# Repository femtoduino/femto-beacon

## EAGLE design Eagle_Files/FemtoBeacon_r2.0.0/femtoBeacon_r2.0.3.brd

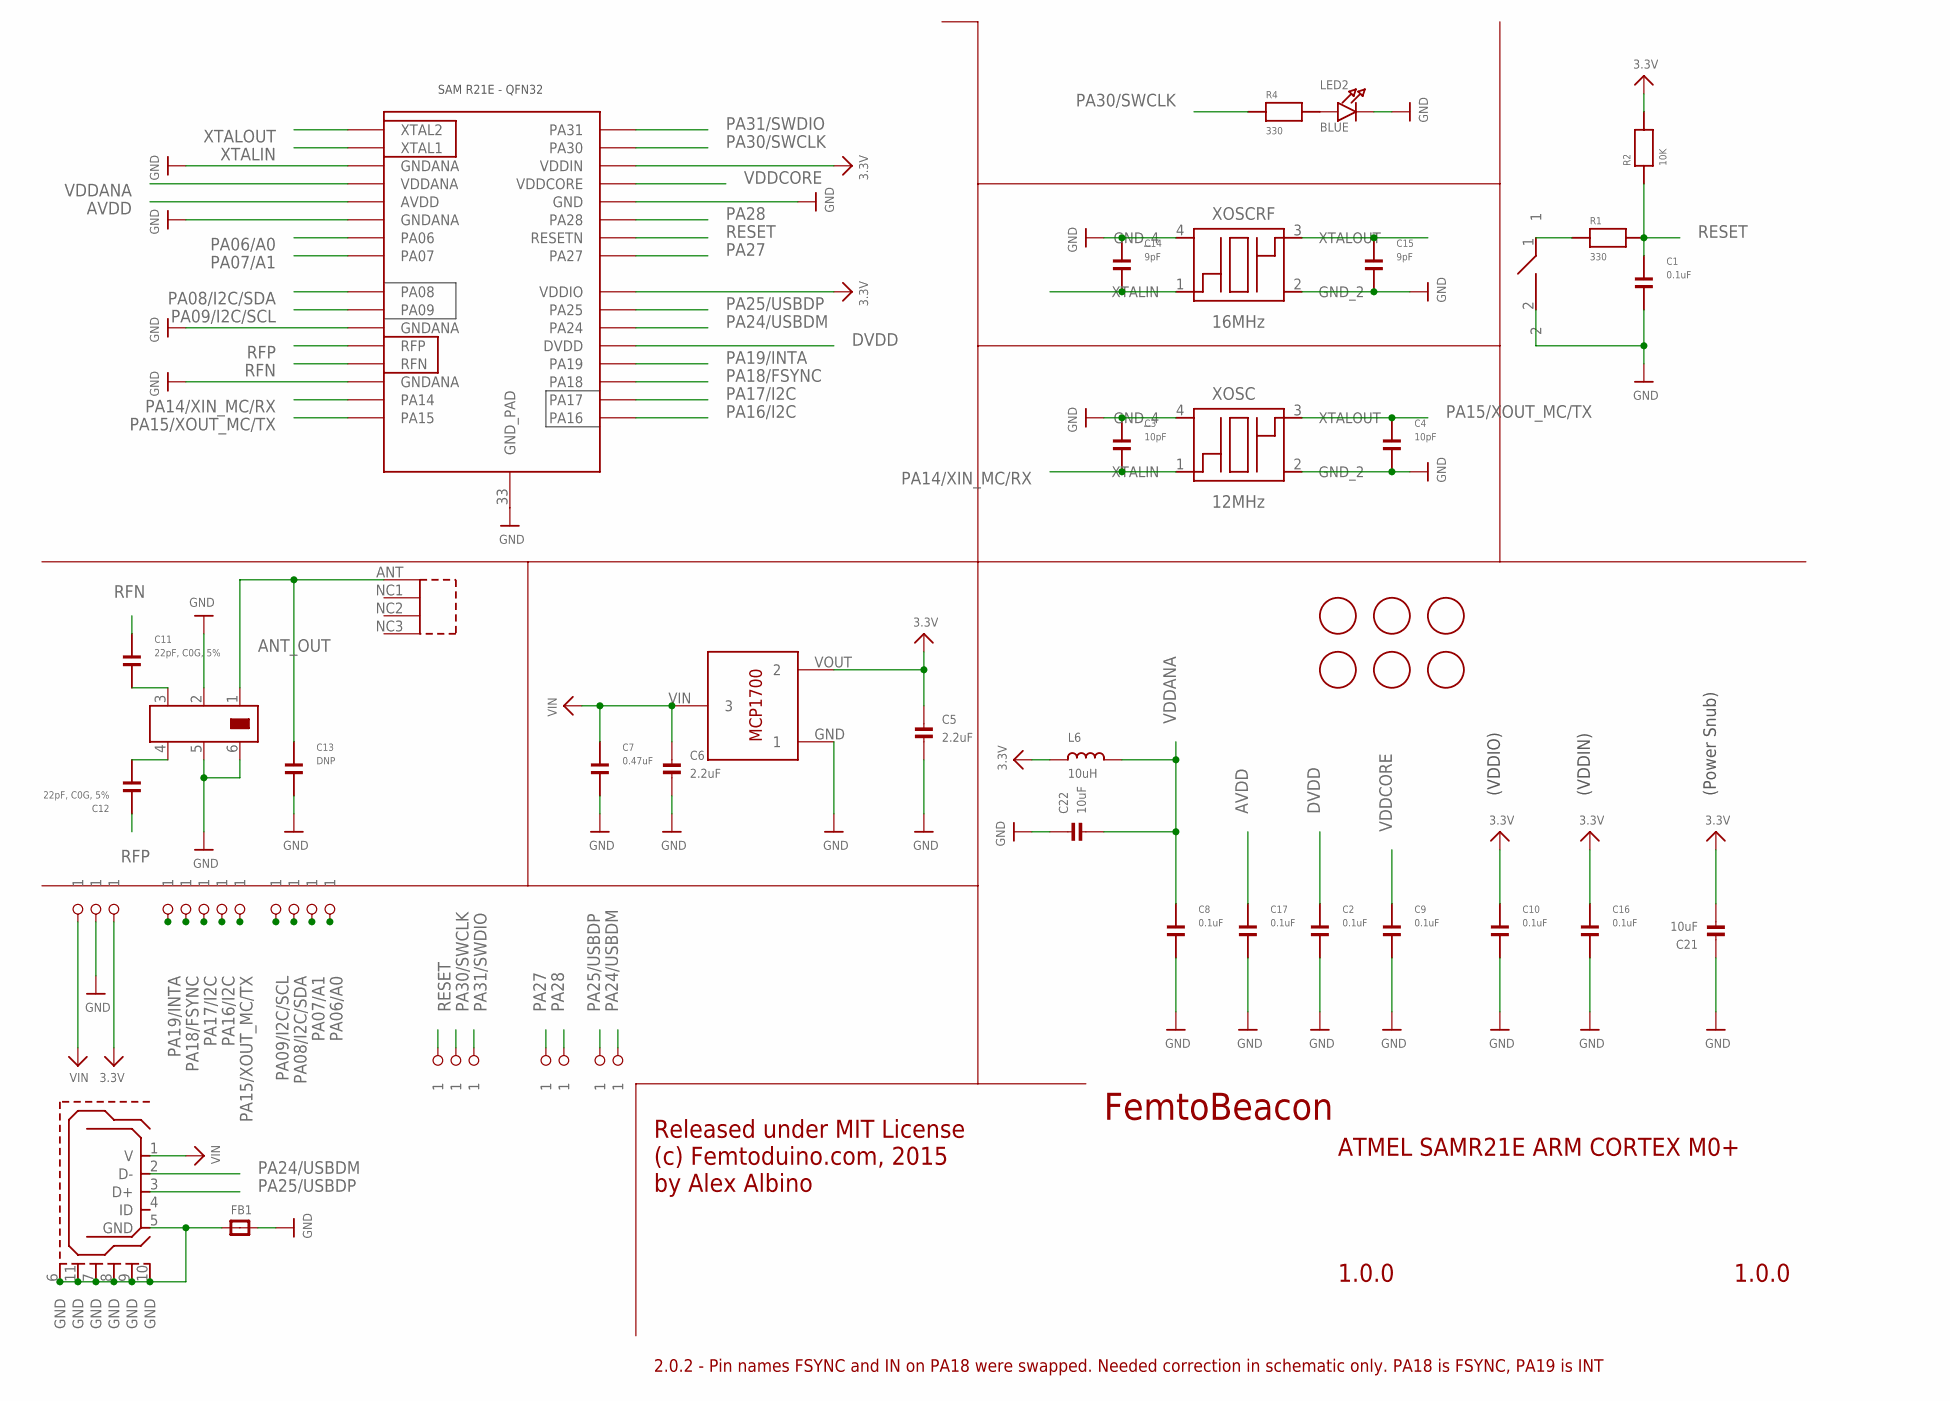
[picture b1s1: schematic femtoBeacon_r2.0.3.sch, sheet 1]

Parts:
BAL: JOHANSON_2450BM15A0015E; 0805_BALUN
BTN: DNP; SPST_SMD
C1, C8, C9, C10, C16, C17: 0.1uF; PART; DIGIKEY_PART 490-3194-1-ND
C2: 0.1uF; PART
C3, C4: 10pF; PART; DIGIKEY_PART 490-3194-1-ND
C5, C6: 2.2uF; _0402MP
C7: 0.47uF; PART
C11, C12: 22pF, C0G, 5%; PART; DIGIKEY_PART 490-3194-1-ND
C13: DNP; PART; DIGIKEY_PART 490-3194-1-ND
C14, C15: 9pF; PART; DIGIKEY_PART 490-3194-1-ND
C21, C22: 10uF; _0402MP
FB1: FERRITE_0603MP; _0603MP
FID1, FID2, FID3, FID4, FID5, FID6: FIDUCIAL; FIDUCIAL_1MM
IC: ATSAMR21E18A-MUT; QFN32
L6: 10uH; _0603MP
LDO_VREG: MCP1700T-3302E/TT
LED2: BLUE; CHIPLED_0603_NOOUTLINE
R1, R4: 330; PART
R2: 10K; PART
U$1, U$2, U$5, U$7, U$9, U$10, U$35, U$36, U$37, U$38, U$39, U$41, U$42, U$43, U$45, U$46, U$47, U$48, U$54: 1X1_ROUND
U$8: 0479480001
USB: USB_MICROB; USB_MICROB_PACKAGE
XOSC: 12MHz; TSX-3225
XOSCRF: 16MHz; TSX-3225

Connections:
3.3V: C5.1, C10.1, C16.1, C21.2, IC.24 (VDDIO), IC.30 (VDDIN), L6.1, LDO_VREG.VOUT (2), R2.2, U$5.P$1; also elsewhere on the board
ANT_OUT: BAL.1, C13.1, U$8.ANT (1)
AVDD: C17.1, IC.5 (AVDD)
DVDD: C2.1, IC.21 (DVDD)
GND: BAL.2, BAL.5, BAL.6, BTN.2, C1.2, C2.2, C3.1, C4.2, C5.2, C6.2, C7.2, C8.2, C9.2, C10.2, C13.2, C14.1, C15.2, C16.2, C17.2, C21.1, C22.1, FB1.2, IC.3 (GNDANA), IC.6 (GNDANA), IC.11 (GNDANA), IC.14 (GNDANA), IC.28 (GND), IC.33 (GND_PAD), LDO_VREG.GND (1), LED2.C, U$2.P$1, XOSC.2 (GND_2), XOSC.4 (GND_4), XOSCRF.2 (GND_2), XOSCRF.4 (GND_4); also elsewhere on the board
unnamed: BAL.3, C11.2
unnamed: BAL.4, C12.2
unnamed: FB1.1, USB.5 (GND), USB.6 (GND), USB.7 (GND), USB.8 (GND), USB.9 (GND), USB.10 (GND), USB.11 (GND)
unnamed: LED2.A, R4.2
unnamed: BTN.1, R1.1
PA06/A0: IC.7 (PA06), U$54.P$1
PA07/A1: IC.8 (PA07), U$43.P$1
PA08/I2C/SDA: IC.9 (PA08), U$42.P$1; also elsewhere on the board
PA09/I2C/SCL: IC.10 (PA09), U$41.P$1; also elsewhere on the board
PA14/XIN_MC/RX: C3.2, IC.15 (PA14), XOSC.1 (XTALIN)
PA15/XOUT_MC/TX: C4.1, IC.16 (PA15), U$39.P$1, XOSC.3 (XTALOUT)
PA16/I2C: IC.17 (PA16), U$38.P$1
PA17/I2C: IC.18 (PA17), U$37.P$1
PA18/FSYNC: IC.19 (PA18), U$36.P$1; also elsewhere on the board
PA19/INTA: IC.20 (PA19), U$35.P$1; also elsewhere on the board
PA24/USBDM: IC.22 (PA24), U$9.P$1, USB.2 (D-)
PA25/USBDP: IC.23 (PA25), U$10.P$1, USB.3 (D+)
PA27: IC.25 (PA27), U$7.P$1
PA28: IC.27 (PA28), U$48.P$1
PA30/SWCLK: IC.31 (PA30), R4.1, U$46.P$1
PA31/SWDIO: IC.32 (PA31), U$47.P$1
RESET: C1.1, IC.26 (RESETN), R1.2, R2.1, U$45.P$1
RFN: C11.1, IC.13 (RFN)
RFP: C12.1, IC.12 (RFP)
VDDANA: C8.1, C22.2, IC.4 (VDDANA), L6.2
VDDCORE: C9.1, IC.29 (VDDCORE)
VIN: C6.1, C7.1, LDO_VREG.VIN (3), U$1.P$1, USB.1 (V)
XTALIN: C14.2, IC.2 (XTAL1), XOSCRF.1 (XTALIN)
XTALOUT: C15.1, IC.1 (XTAL2), XOSCRF.3 (XTALOUT)

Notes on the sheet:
FemtoBeacon
1.0.0
ATMEL SAMR21E ARM CORTEX M0+
Released under MIT License (c) Femtoduino.com, 2015 by Alex Albino
(Power Snub)
(VDDIO)
(VDDIN)
2.0.2 - Pin names FSYNC and IN on PA18 were swapped. Needed correction in schematic only. PA18 is FSYNC, PA19 is INT

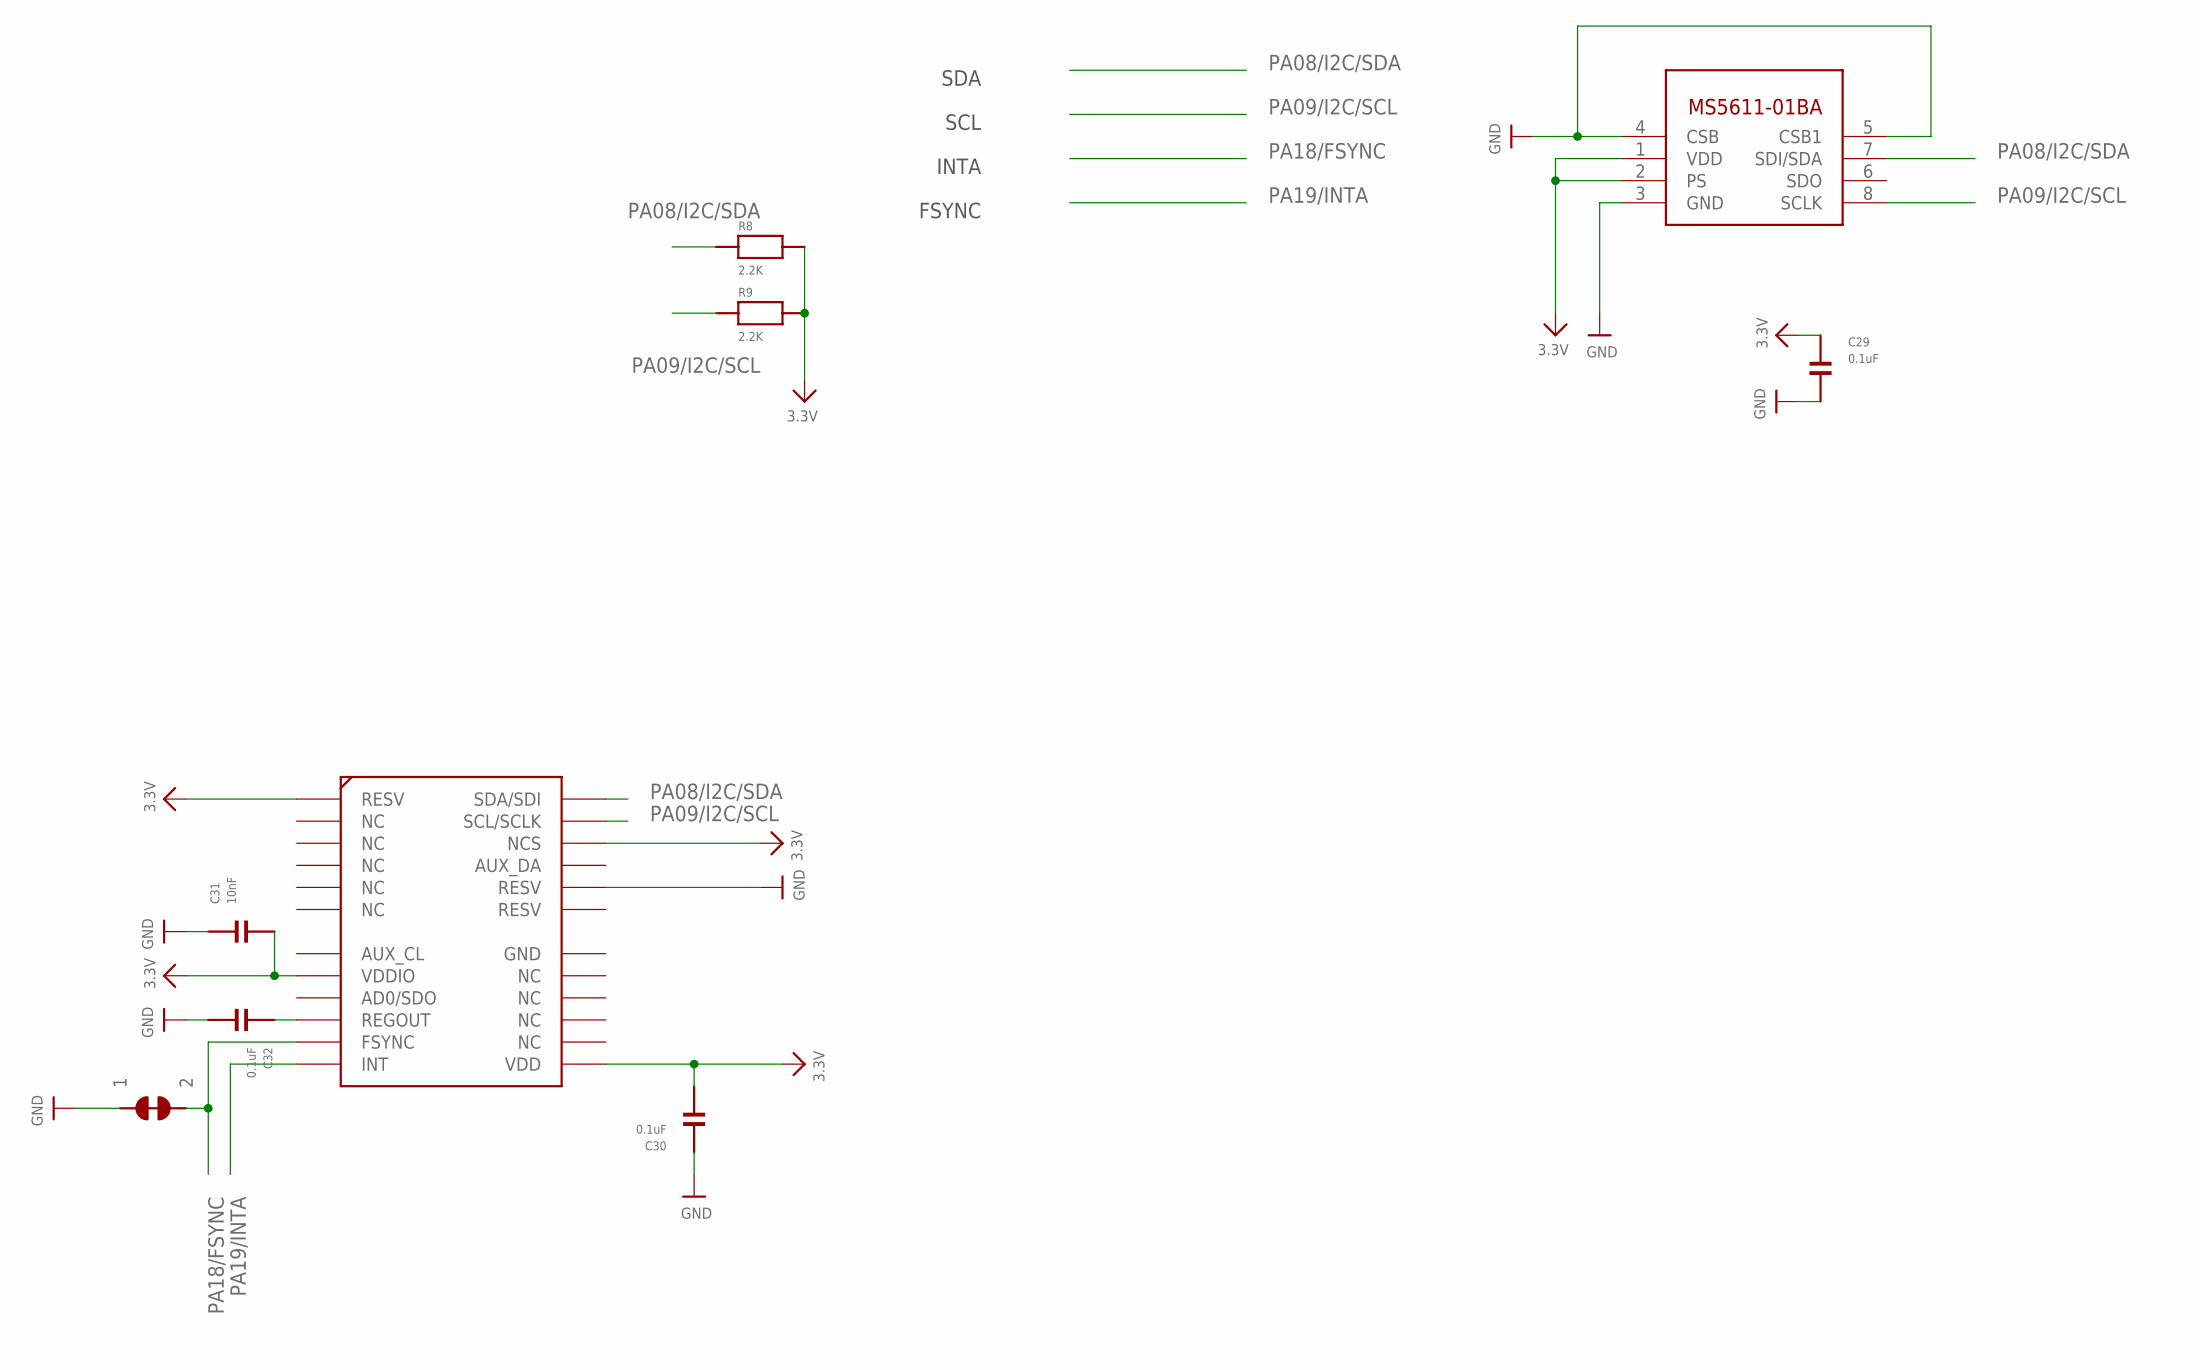
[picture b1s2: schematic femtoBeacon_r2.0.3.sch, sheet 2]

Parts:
BARO: MS5611-01BA03
C29, C30, C32: 0.1uF; PART; DIGIKEY_PART 490-3194-1-ND
C31: 10nF; PART; DIGIKEY_PART 490-3194-1-ND
IMU: MPU-9250; QFN_3X3MM
R8, R9: 2.2K; PART
SJ1: SOLDER_JUMPER_CLOSED; SOLDER_JUMP_CLOSED

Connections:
3.3V: BARO.1 (VDD), BARO.2 (PS), C29.1, C30.2, C31.2, IMU.P$1 (RESV), IMU.P$8 (VDDIO), IMU.P$13 (VDD), IMU.P$22 (NCS), R8.2, R9.2; also elsewhere on the board
GND: BARO.3 (GND), BARO.4 (CSB), BARO.5 (CSB1), C29.2, C30.1, C31.1, C32.2, IMU.P$20 (RESV), SJ1.1; also elsewhere on the board
unnamed: C32.1, IMU.P$10 (REGOUT)
PA08/I2C/SDA: BARO.7 (SDI/SDA), IMU.P$24 (SDA/SDI), R8.1; also elsewhere on the board
PA09/I2C/SCL: BARO.8 (SCLK), IMU.P$23 (SCL/SCLK), R9.1; also elsewhere on the board
PA18/FSYNC: IMU.P$11 (FSYNC), SJ1.2; also elsewhere on the board
PA19/INTA: IMU.P$12 (INT); also elsewhere on the board

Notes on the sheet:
SDA
SCL
INTA
FSYNC

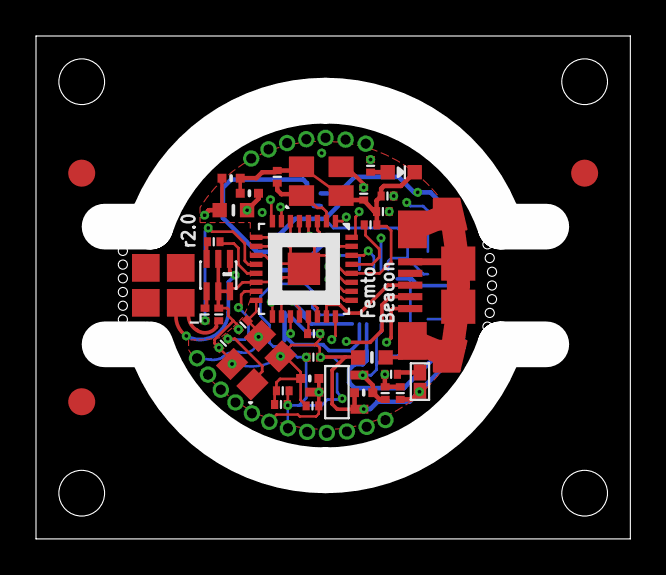
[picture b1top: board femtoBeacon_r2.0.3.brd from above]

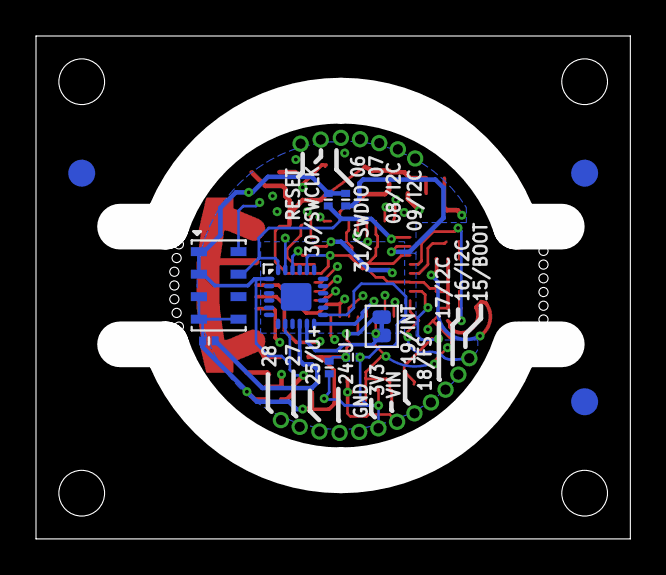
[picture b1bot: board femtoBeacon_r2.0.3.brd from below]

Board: 4 copper layers, 33.0 x 27.9 mm, 67 parts (11 on the bottom side), 35 nets.

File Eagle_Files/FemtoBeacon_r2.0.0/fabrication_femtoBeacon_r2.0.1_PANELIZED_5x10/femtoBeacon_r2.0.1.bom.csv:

"Qty","Value","Device","Package","Parts","Description","DIGIKEY_PART"
"1",,"FERRITE_0603MP","_0603MP","FB1","Ferrite Bead",
"10","0.1uF","CAPACITOR_0201","PART","C1, C2, C8, C9, C10, C16, C17, C29, C30, C32",,"490-3194-1-ND"
"1","0.47uF","CAPACITOR_0201","PART","C7",,
"1","10K","RESISTOR_0201","PART","R2",,
"1","10nF","CAPACITOR_0201","PART","C31",,"490-3194-1-ND"
"2","10pF","CAPACITOR_0201","PART","C3, C4",,"490-3194-1-ND"
"2","10uF","CAP_CERAMIC_0402MP","_0402MP","C21, C22","Ceramic Capacitors",
"1","10uH","INDUCTOR_0603MP","_0603MP","L6","Inductors",
"1","12MHz","TSX-3225","TSX-3225","XOSC",,
"1","16MHz","TSX-3225","TSX-3225","XOSCRF",,
"2","2.2K","RESISTOR_0201","PART","R8, R9",,
"2","2.2uF","CAP_CERAMIC_0402MP","_0402MP","C5, C6","Ceramic Capacitors",
"2","22pF, C0G, 5%","CAPACITOR_0201","PART","C11, C12",,"490-3194-1-ND"
"2","330","RESISTOR_0201","PART","R1, R4",,
"2","9pF","CAPACITOR_0201","PART","C14, C15",,"490-3194-1-ND"
"1","ATSAMR21E18A-MUT","ATSAMR21E18A-MUT","QFN32","IC","This is the ATMEL SAMR21E QFN-32. ATSAMR21E18A",
"1","BLUE","LED0603_NOOUTLINE","CHIPLED_0603_NOOUTLINE","LED2","LED",
"1","JOHANSON_2450BM15A0015E","JOHANSON_2450BM15A0015E","0805_BALUN","BAL",,
"1","MCP1700T-3302E/TT","MCP1700T-3302E/TT","MCP1700T-3302E/TT","LDO_VREG","Microchip LDO ""MCP1700"" in a 3-Pin SOT-23 package.",
"1","MPU-9250","MPU-9250","QFN_3X3MM","IMU",,
"1","MS5611-01BA03","MS5611-01BA03","MS5611-01BA03","BARO",,
"1","PULSE_ANT_2.4GHZ","PULSE_ANT_2.4GHZ","ANT_BAR","ANT1","Manufacturer part #W3008",
"1","USB_MICROB","USB_MICROB","USB_MICROB_PACKAGE","USB","This is the hirose ZX62-B-5PA(11) MICRO-USB B Type female connection.",

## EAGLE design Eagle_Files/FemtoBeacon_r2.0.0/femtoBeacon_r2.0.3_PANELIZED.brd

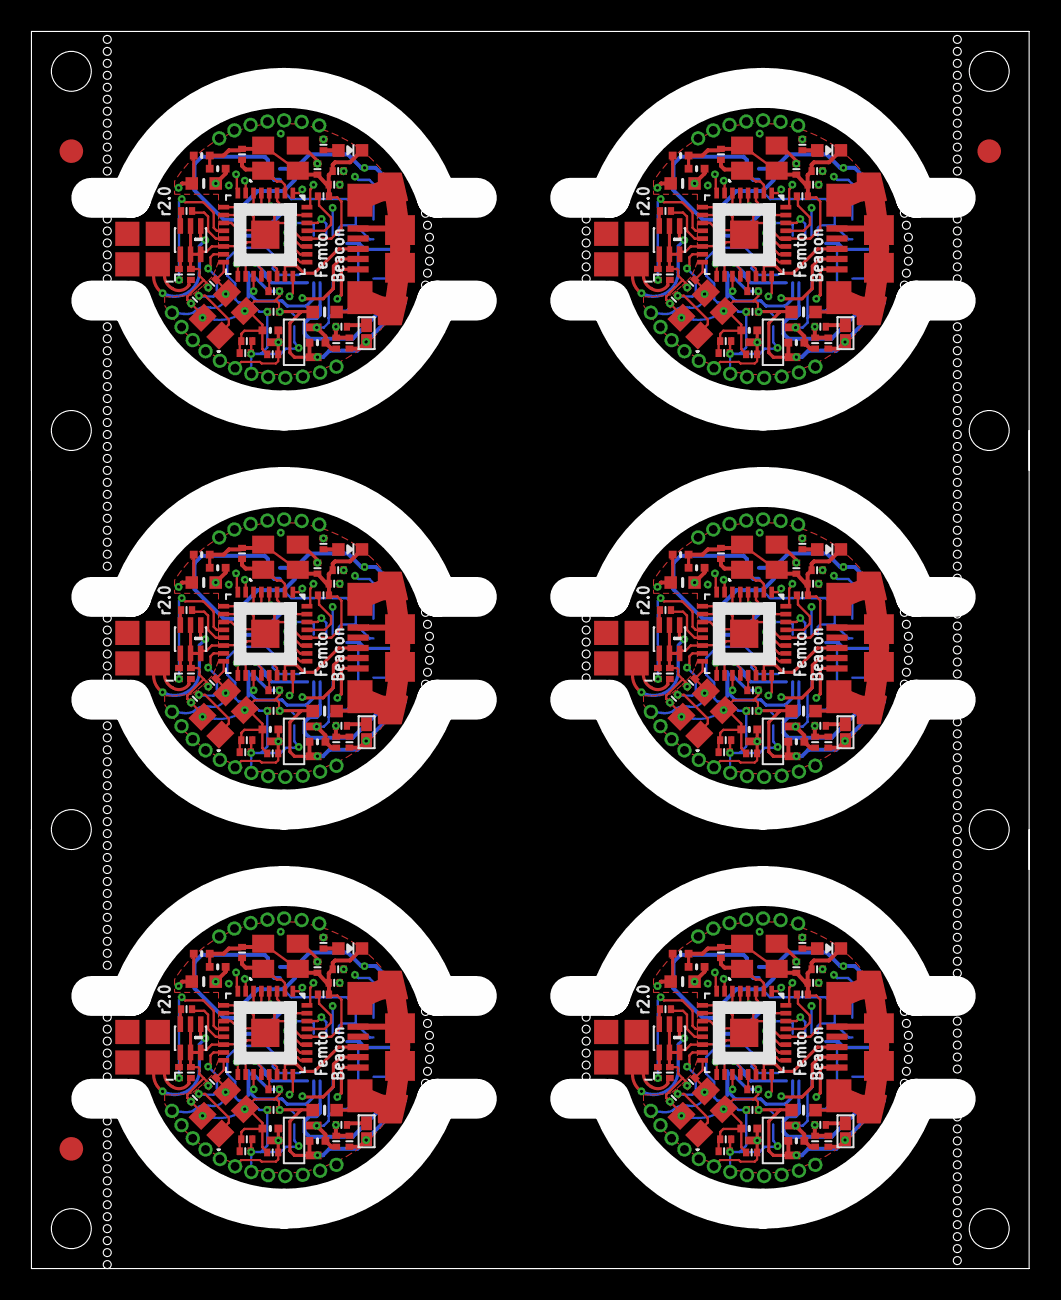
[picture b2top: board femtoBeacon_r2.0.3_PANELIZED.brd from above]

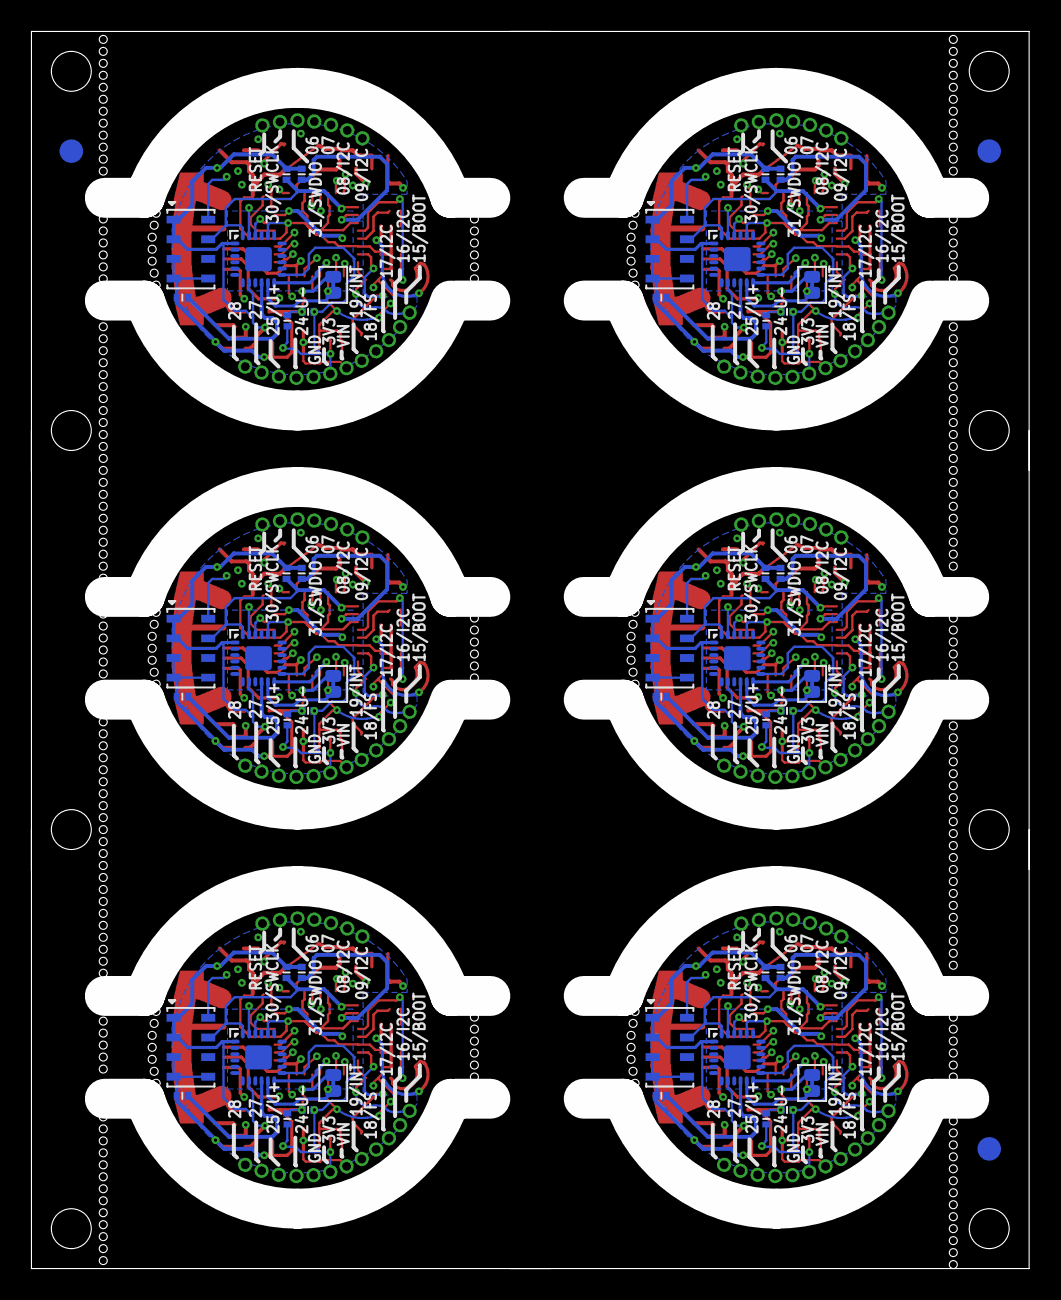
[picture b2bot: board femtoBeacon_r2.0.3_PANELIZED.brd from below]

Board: 4 copper layers, 63.5 x 78.7 mm, 372 parts (51 on the bottom side), 210 nets.

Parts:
BAL, BAL1, BAL2, BAL3, BAL4, BAL5: JOHANSON_2450BM15A0015E; 0805_BALUN
BARO, BARO1, BARO2, BARO3, BARO4, BARO5: MS5611-01BA03
BTN, BTN1, BTN2, BTN3, BTN4, BTN5: DNP; SPST_SMD
C1, C2, C8, C9, C10, C16, C17, C18, C19, C25, C26, C27, C28, C29, C30, C32, C33, C36, C45, C46, C47, C48, C52, C53, C54, C55, C56, C59, C68, C69, C70, C71, C75, C76, C77, C78, C79, C82, C91, C92, C93, C94, C98, C99, C100, C101, C102, C105, C114, C115, C116, C117, C121, C122, C123, C124, C125, C128, C137, C138: 0.1uF; PART
C3, C4, C37, C38, C60, C61, C83, C84, C106, C107, C129, C130: 10pF; PART
C5, C6, C20, C23, C49, C50, C72, C73, C95, C96, C118, C119: 2.2uF; _0402MP
C7, C24, C51, C74, C97, C120: 0.47uF; PART
C11, C12, C39, C40, C62, C63, C85, C86, C108, C109, C131, C132: 22pF, C0G, 5%; PART
C13, C41, C64, C87, C110, C133: DNP; PART
C14, C15, C42, C43, C65, C66, C88, C89, C111, C112, C134, C135: 9pF; PART
C21, C22, C34, C35, C57, C58, C80, C81, C103, C104, C126, C127: 10uF; _0402MP
C31, C44, C67, C90, C113, C136: 10nF; PART
FB1, FB2, FB3, FB4, FB5, FB6: _0603MP
FID1, FID2, FID3, FID4, FID5, FID6: FIDUCIAL; FIDUCIAL_1MM
IC, IC1, IC2, IC3, IC4, IC5: ATSAMR21E18A-MUT; QFN32
IMU, IMU1, IMU2, IMU3, IMU4, IMU5: MPU-9250; QFN_3X3MM
L1, L2, L3, L4, L5, L6: 10uH; _0603MP
LDO_VREG, LDO_VREG1, LDO_VREG2, LDO_VREG3, LDO_VREG4, LDO_VREG5: MCP1700T-3302E/TT
LED1, LED2, LED3, LED4, LED5, LED6: BLUE; CHIPLED_0603_NOOUTLINE
R1, R3, R4, R6, R11, R13, R16, R18, R21, R23, R26, R28: 330; PART
R2, R5, R12, R17, R22, R27: 10K; PART
R7, R8, R9, R10, R14, R15, R19, R20, R24, R25, R29, R30: 2.2K; PART
SJ1, SJ2, SJ3, SJ4, SJ5, SJ6: SOLDER_JUMPER_CLOSED; SOLDER_JUMP_CLOSED
U$1, U$2, U$3, U$4, U$5, U$6, U$7, U$9, U$10, U$11, U$12, U$13, U$14, U$15, U$16, U$17, U$18, U$19, U$20, U$21, U$22, U$23, U$24, U$25, U$26, U$28, U$29, U$30, U$31, U$32, U$33, U$34, U$35, U$36, U$37, U$38, U$39, U$40, U$41, U$42, U$43, U$44, U$45, U$46, U$47, U$48, U$49, U$50, U$51, U$52, U$53, U$54, U$55, U$56, U$57, U$58, U$59, U$61, U$62, U$63, U$64, U$65, U$66, U$67, U$68, U$69, U$70, U$71, U$72, U$73, U$74, U$75, U$76, U$77, U$78, U$79, U$81, U$82, U$83, U$84, U$85, U$86, U$87, U$88, U$89, U$90, U$91, U$92, U$93, U$94, U$95, U$96, U$97, U$98, U$99, U$101, U$102, U$103, U$104, U$105, U$106, U$107, U$108, U$109, U$110, U$111, U$112, U$113, U$114, U$115, U$116, U$117, U$118, U$119: 1X1_ROUND
U$8, U$27, U$60, U$80, U$100, U$120: 0479480001
USB, USB1, USB2, USB3, USB4, USB5: USB_MICROB; USB_MICROB_PACKAGE
XOSC, XOSC1, XOSC2, XOSC3, XOSC4, XOSC5: 12MHz; TSX-3225
XOSCRF, XOSCRF1, XOSCRF2, XOSCRF3, XOSCRF4, XOSCRF5: 16MHz; TSX-3225

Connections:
3.3V: BARO.1, BARO.2, C5.1, C10.1, C16.1, C21.2, C29.1, C30.2, C31.2, IC.24, IC.30, IMU.P$1, IMU.P$8, IMU.P$13, IMU.P$22, L6.1, LDO_VREG.VOUT, R2.2, R8.2, R9.2, U$5.P$1
3.3V1: BARO1.1, BARO1.2, C20.1, C25.1, C28.1, C34.2, C36.1, C44.2, C45.2, IC1.24, IC1.30, IMU1.P$1, IMU1.P$8, IMU1.P$13, IMU1.P$22, L1.1, LDO_VREG1.VOUT, R5.2, R7.2, R10.2, U$6.P$1
3.3V2: BARO2.1, BARO2.2, C49.1, C52.1, C55.1, C57.2, C59.1, C67.2, C68.2, IC2.24, IC2.30, IMU2.P$1, IMU2.P$8, IMU2.P$13, IMU2.P$22, L2.1, LDO_VREG2.VOUT, R12.2, R14.2, R15.2, U$30.P$1
3.3V3: BARO3.1, BARO3.2, C72.1, C75.1, C78.1, C80.2, C82.1, C90.2, C91.2, IC3.24, IC3.30, IMU3.P$1, IMU3.P$8, IMU3.P$13, IMU3.P$22, L3.1, LDO_VREG3.VOUT, R17.2, R19.2, R20.2, U$63.P$1
3.3V4: BARO4.1, BARO4.2, C95.1, C98.1, C101.1, C103.2, C105.1, C113.2, C114.2, IC4.24, IC4.30, IMU4.P$1, IMU4.P$8, IMU4.P$13, IMU4.P$22, L4.1, LDO_VREG4.VOUT, R22.2, R24.2, R25.2, U$83.P$1
3.3V5: BARO5.1, BARO5.2, C118.1, C121.1, C124.1, C126.2, C128.1, C136.2, C137.2, IC5.24, IC5.30, IMU5.P$1, IMU5.P$8, IMU5.P$13, IMU5.P$22, L5.1, LDO_VREG5.VOUT, R27.2, R29.2, R30.2, U$103.P$1
ANT_OUT: BAL.1, C13.1, U$8.ANT
ANT_OUT1: BAL1.1, C41.1, U$27.ANT
ANT_OUT2: BAL2.1, C64.1, U$60.ANT
ANT_OUT3: BAL3.1, C87.1, U$80.ANT
ANT_OUT4: BAL4.1, C110.1, U$100.ANT
ANT_OUT5: BAL5.1, C133.1, U$120.ANT
AVDD: C17.1, IC.5
AVDD1: C33.1, IC1.5
AVDD2: C56.1, IC2.5
AVDD3: C79.1, IC3.5
AVDD4: C102.1, IC4.5
AVDD5: C125.1, IC5.5
DVDD: C2.1, IC.21
DVDD1: C19.1, IC1.21
DVDD2: C48.1, IC2.21
DVDD3: C71.1, IC3.21
DVDD4: C94.1, IC4.21
DVDD5: C117.1, IC5.21
GND: BAL.2, BAL.5, BAL.6, BARO.3, BARO.4, BARO.5, BTN.2, C1.2, C2.2, C3.1, C4.2, C5.2, C6.2, C7.2, C8.2, C9.2, C10.2, C13.2, C14.1, C15.2, C16.2, C17.2, C21.1, C22.1, C29.2, C30.1, C31.1, C32.2, FB1.2, IC.3, IC.6, IC.11, IC.14, IC.28, IC.33, IMU.P$20, LDO_VREG.GND, LED2.C, SJ1.1, U$2.P$1, XOSC.2, XOSC.4, XOSCRF.2, XOSCRF.4
GND1: BAL1.2, BAL1.5, BAL1.6, BARO1.3, BARO1.4, BARO1.5, BTN1.2, C18.2, C19.2, C20.2, C23.2, C24.2, C25.2, C26.2, C27.2, C28.2, C33.2, C34.1, C35.1, C36.2, C37.1, C38.2, C41.2, C42.1, C43.2, C44.1, C45.1, C46.2, FB2.2, IC1.3, IC1.6, IC1.11, IC1.14, IC1.28, IC1.33, IMU1.P$20, LDO_VREG1.GND, LED1.C, SJ2.1, U$4.P$1, XOSC1.2, XOSC1.4, XOSCRF1.2, XOSCRF1.4
GND2: BAL2.2, BAL2.5, BAL2.6, BARO2.3, BARO2.4, BARO2.5, BTN2.2, C47.2, C48.2, C49.2, C50.2, C51.2, C52.2, C53.2, C54.2, C55.2, C56.2, C57.1, C58.1, C59.2, C60.1, C61.2, C64.2, C65.1, C66.2, C67.1, C68.1, C69.2, FB3.2, IC2.3, IC2.6, IC2.11, IC2.14, IC2.28, IC2.33, IMU2.P$20, LDO_VREG2.GND, LED3.C, SJ3.1, U$29.P$1, XOSC2.2, XOSC2.4, XOSCRF2.2, XOSCRF2.4
GND3: BAL3.2, BAL3.5, BAL3.6, BARO3.3, BARO3.4, BARO3.5, BTN3.2, C70.2, C71.2, C72.2, C73.2, C74.2, C75.2, C76.2, C77.2, C78.2, C79.2, C80.1, C81.1, C82.2, C83.1, C84.2, C87.2, C88.1, C89.2, C90.1, C91.1, C92.2, FB4.2, IC3.3, IC3.6, IC3.11, IC3.14, IC3.28, IC3.33, IMU3.P$20, LDO_VREG3.GND, LED4.C, SJ4.1, U$62.P$1, XOSC3.2, XOSC3.4, XOSCRF3.2, XOSCRF3.4
GND4: BAL4.2, BAL4.5, BAL4.6, BARO4.3, BARO4.4, BARO4.5, BTN4.2, C93.2, C94.2, C95.2, C96.2, C97.2, C98.2, C99.2, C100.2, C101.2, C102.2, C103.1, C104.1, C105.2, C106.1, C107.2, C110.2, C111.1, C112.2, C113.1, C114.1, C115.2, FB5.2, IC4.3, IC4.6, IC4.11, IC4.14, IC4.28, IC4.33, IMU4.P$20, LDO_VREG4.GND, LED5.C, SJ5.1, U$82.P$1, XOSC4.2, XOSC4.4, XOSCRF4.2, XOSCRF4.4
GND5: BAL5.2, BAL5.5, BAL5.6, BARO5.3, BARO5.4, BARO5.5, BTN5.2, C116.2, C117.2, C118.2, C119.2, C120.2, C121.2, C122.2, C123.2, C124.2, C125.2, C126.1, C127.1, C128.2, C129.1, C130.2, C133.2, C134.1, C135.2, C136.1, C137.1, C138.2, FB6.2, IC5.3, IC5.6, IC5.11, IC5.14, IC5.28, IC5.33, IMU5.P$20, LDO_VREG5.GND, LED6.C, SJ6.1, U$102.P$1, XOSC5.2, XOSC5.4, XOSCRF5.2, XOSCRF5.4
unnamed: BAL.3, C11.2
unnamed: BTN1.1, R3.1
unnamed: BAL.4, C12.2
unnamed: C32.1, IMU.P$10
unnamed: FB1.1, USB.5, USB.6, USB.7, USB.8, USB.9, USB.10, USB.11
unnamed: LED1.A, R6.2
unnamed: BAL1.3, C39.2
unnamed: BAL1.4, C40.2
unnamed: C46.1, IMU1.P$10
unnamed: FB2.1, USB1.5, USB1.6, USB1.7, USB1.8, USB1.9, USB1.10, USB1.11
unnamed: BTN2.1, R11.1
unnamed: LED3.A, R13.2
unnamed: LED2.A, R4.2
unnamed: BAL2.3, C62.2
unnamed: BAL2.4, C63.2
unnamed: C69.1, IMU2.P$10
unnamed: FB3.1, USB2.5, USB2.6, USB2.7, USB2.8, USB2.9, USB2.10, USB2.11
unnamed: BTN3.1, R16.1
unnamed: LED4.A, R18.2
unnamed: BAL3.3, C85.2
unnamed: BAL3.4, C86.2
unnamed: C92.1, IMU3.P$10
unnamed: FB4.1, USB3.5, USB3.6, USB3.7, USB3.8, USB3.9, USB3.10, USB3.11
unnamed: BTN4.1, R21.1
unnamed: LED5.A, R23.2
unnamed: BTN.1, R1.1
unnamed: BAL4.3, C108.2
unnamed: BAL4.4, C109.2
unnamed: C115.1, IMU4.P$10
unnamed: FB5.1, USB4.5, USB4.6, USB4.7, USB4.8, USB4.9, USB4.10, USB4.11
unnamed: BTN5.1, R26.1
unnamed: LED6.A, R28.2
unnamed: BAL5.3, C131.2
unnamed: BAL5.4, C132.2
unnamed: C138.1, IMU5.P$10
unnamed: FB6.1, USB5.5, USB5.6, USB5.7, USB5.8, USB5.9, USB5.10, USB5.11
PA1: IC1.25, U$22.P$1
PA2: IC1.27, U$23.P$1
PA3: IC2.25, U$55.P$1
PA4: IC2.27, U$56.P$1
PA5: IC3.25, U$75.P$1
PA6: IC3.27, U$76.P$1
PA06/A0: IC.7, U$54.P$1
PA06/A1: IC1.7, U$24.P$1
PA06/A2: IC2.7, U$57.P$1
PA06/A3: IC3.7, U$77.P$1
PA06/A4: IC4.7, U$97.P$1
PA06/A5: IC5.7, U$117.P$1
PA7: IC4.25, U$95.P$1
PA07/A1: IC.8, U$43.P$1
PA07/A2: IC1.8, U$18.P$1
PA07/A3: IC2.8, U$50.P$1
PA07/A4: IC3.8, U$71.P$1
PA07/A5: IC4.8, U$91.P$1
PA07/A6: IC5.8, U$111.P$1
PA8: IC4.27, U$96.P$1
PA08/I2C/SDA: BARO.7, IC.9, IMU.P$24, R8.1, U$42.P$1
PA08/I2C/SDA1: BARO1.7, IC1.9, IMU1.P$24, R7.1, U$17.P$1
PA08/I2C/SDA2: BARO2.7, IC2.9, IMU2.P$24, R14.1, U$49.P$1
PA08/I2C/SDA3: BARO3.7, IC3.9, IMU3.P$24, R19.1, U$70.P$1
PA08/I2C/SDA4: BARO4.7, IC4.9, IMU4.P$24, R24.1, U$90.P$1
PA08/I2C/SDA5: BARO5.7, IC5.9, IMU5.P$24, R29.1, U$110.P$1
PA9: IC5.25, U$115.P$1
PA09/I2C/SCL: BARO.8, IC.10, IMU.P$23, R9.1, U$41.P$1
PA09/I2C/SCL1: BARO1.8, IC1.10, IMU1.P$23, R10.1, U$16.P$1
PA09/I2C/SCL2: BARO2.8, IC2.10, IMU2.P$23, R15.1, U$44.P$1
PA09/I2C/SCL3: BARO3.8, IC3.10, IMU3.P$23, R20.1, U$69.P$1
PA09/I2C/SCL4: BARO4.8, IC4.10, IMU4.P$23, R25.1, U$89.P$1
PA09/I2C/SCL5: BARO5.8, IC5.10, IMU5.P$23, R30.1, U$109.P$1
PA10: IC5.27, U$116.P$1
PA14/XIN_MC/RX: C3.2, IC.15, XOSC.1
PA14/XIN_MC/RX1: C37.2, IC1.15, XOSC1.1
PA14/XIN_MC/RX2: C60.2, IC2.15, XOSC2.1
PA14/XIN_MC/RX3: C83.2, IC3.15, XOSC3.1
PA14/XIN_MC/RX4: C106.2, IC4.15, XOSC4.1
PA14/XIN_MC/RX5: C129.2, IC5.15, XOSC5.1
PA15/XOUT_MC/TX: C4.1, IC.16, U$39.P$1, XOSC.3
PA15/XOUT_MC/TX1: C38.1, IC1.16, U$15.P$1, XOSC1.3
PA15/XOUT_MC/TX2: C61.1, IC2.16, U$40.P$1, XOSC2.3
PA15/XOUT_MC/TX3: C84.1, IC3.16, U$68.P$1, XOSC3.3
PA15/XOUT_MC/TX4: C107.1, IC4.16, U$88.P$1, XOSC4.3
PA15/XOUT_MC/TX5: C130.1, IC5.16, U$108.P$1, XOSC5.3
PA16/I2C: IC.17, U$38.P$1
PA16/I2C1: IC1.17, U$14.P$1
PA16/I2C2: IC2.17, U$34.P$1
PA16/I2C3: IC3.17, U$67.P$1
PA16/I2C4: IC4.17, U$87.P$1
PA16/I2C5: IC5.17, U$107.P$1
PA17/I2C: IC.18, U$37.P$1
PA17/I2C1: IC1.18, U$13.P$1
PA17/I2C2: IC2.18, U$33.P$1
PA17/I2C3: IC3.18, U$66.P$1
PA17/I2C4: IC4.18, U$86.P$1
PA17/I2C5: IC5.18, U$106.P$1
PA18/FSYNC: IC.19, IMU.P$11, SJ1.2, U$36.P$1
PA18/FSYNC1: IC1.19, IMU1.P$11, SJ2.2, U$12.P$1
PA18/FSYNC2: IC2.19, IMU2.P$11, SJ3.2, U$32.P$1
PA18/FSYNC3: IC3.19, IMU3.P$11, SJ4.2, U$65.P$1
PA18/FSYNC4: IC4.19, IMU4.P$11, SJ5.2, U$85.P$1
PA18/FSYNC5: IC5.19, IMU5.P$11, SJ6.2, U$105.P$1
PA19/INTA: IC.20, IMU.P$12, U$35.P$1
PA19/INTA1: IC1.20, IMU1.P$12, U$11.P$1
PA19/INTA2: IC2.20, IMU2.P$12, U$31.P$1
PA19/INTA3: IC3.20, IMU3.P$12, U$64.P$1
PA19/INTA4: IC4.20, IMU4.P$12, U$84.P$1
PA19/INTA5: IC5.20, IMU5.P$12, U$104.P$1
PA24/USBDM: IC.22, U$9.P$1, USB.2
PA24/USBDM1: IC1.22, U$25.P$1, USB1.2
PA24/USBDM2: IC2.22, U$58.P$1, USB2.2
PA24/USBDM3: IC3.22, U$78.P$1, USB3.2
PA24/USBDM4: IC4.22, U$98.P$1, USB4.2
PA24/USBDM5: IC5.22, U$118.P$1, USB5.2
PA25/USBDP: IC.23, U$10.P$1, USB.3
PA25/USBDP1: IC1.23, U$26.P$1, USB1.3
PA25/USBDP2: IC2.23, U$59.P$1, USB2.3
PA25/USBDP3: IC3.23, U$79.P$1, USB3.3
PA25/USBDP4: IC4.23, U$99.P$1, USB4.3
PA25/USBDP5: IC5.23, U$119.P$1, USB5.3
PA27: IC.25, U$7.P$1
PA28: IC.27, U$48.P$1
PA30/SWCLK: IC.31, R4.1, U$46.P$1
PA30/SWCLK1: IC1.31, R6.1, U$20.P$1
PA30/SWCLK2: IC2.31, R13.1, U$52.P$1
PA30/SWCLK3: IC3.31, R18.1, U$73.P$1
PA30/SWCLK4: IC4.31, R23.1, U$93.P$1
PA30/SWCLK5: IC5.31, R28.1, U$113.P$1
PA31/SWDIO: IC.32, U$47.P$1
PA31/SWDIO1: IC1.32, U$21.P$1
PA31/SWDIO2: IC2.32, U$53.P$1
PA31/SWDIO3: IC3.32, U$74.P$1
PA31/SWDIO4: IC4.32, U$94.P$1
PA31/SWDIO5: IC5.32, U$114.P$1
RESET: C1.1, IC.26, R1.2, R2.1, U$45.P$1
RESET1: C18.1, IC1.26, R3.2, R5.1, U$19.P$1
RESET2: C47.1, IC2.26, R11.2, R12.1, U$51.P$1
RESET3: C70.1, IC3.26, R16.2, R17.1, U$72.P$1
RESET4: C93.1, IC4.26, R21.2, R22.1, U$92.P$1
RESET5: C116.1, IC5.26, R26.2, R27.1, U$112.P$1
RFN: C11.1, IC.13
RFN1: C39.1, IC1.13
RFN2: C62.1, IC2.13
RFN3: C85.1, IC3.13
RFN4: C108.1, IC4.13
RFN5: C131.1, IC5.13
RFP: C12.1, IC.12
RFP1: C40.1, IC1.12
RFP2: C63.1, IC2.12
RFP3: C86.1, IC3.12
RFP4: C109.1, IC4.12
RFP5: C132.1, IC5.12
VDDANA: C8.1, C22.2, IC.4, L6.2
VDDANA1: C26.1, C35.2, IC1.4, L1.2
VDDANA2: C53.1, C58.2, IC2.4, L2.2
VDDANA3: C76.1, C81.2, IC3.4, L3.2
VDDANA4: C99.1, C104.2, IC4.4, L4.2
VDDANA5: C122.1, C127.2, IC5.4, L5.2
VDDCORE: C9.1, IC.29
VDDCORE1: C27.1, IC1.29
VDDCORE2: C54.1, IC2.29
VDDCORE3: C77.1, IC3.29
VDDCORE4: C100.1, IC4.29
VDDCORE5: C123.1, IC5.29
VIN: C6.1, C7.1, LDO_VREG.VIN, U$1.P$1, USB.1
VIN1: C23.1, C24.1, LDO_VREG1.VIN, U$3.P$1, USB1.1
VIN2: C50.1, C51.1, LDO_VREG2.VIN, U$28.P$1, USB2.1
VIN3: C73.1, C74.1, LDO_VREG3.VIN, U$61.P$1, USB3.1
VIN4: C96.1, C97.1, LDO_VREG4.VIN, U$81.P$1, USB4.1
VIN5: C119.1, C120.1, LDO_VREG5.VIN, U$101.P$1, USB5.1
XTALIN: C14.2, IC.2, XOSCRF.1
XTALIN1: C42.2, IC1.2, XOSCRF1.1
XTALIN2: C65.2, IC2.2, XOSCRF2.1
XTALIN3: C88.2, IC3.2, XOSCRF3.1
XTALIN4: C111.2, IC4.2, XOSCRF4.1
XTALIN5: C134.2, IC5.2, XOSCRF5.1
XTALOUT: C15.1, IC.1, XOSCRF.3
XTALOUT1: C43.1, IC1.1, XOSCRF1.3
XTALOUT2: C66.1, IC2.1, XOSCRF2.3
XTALOUT3: C89.1, IC3.1, XOSCRF3.3
XTALOUT4: C112.1, IC4.1, XOSCRF4.3
XTALOUT5: C135.1, IC5.1, XOSCRF5.3

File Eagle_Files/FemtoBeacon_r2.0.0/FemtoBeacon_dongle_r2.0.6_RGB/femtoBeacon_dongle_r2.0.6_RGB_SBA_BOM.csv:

##########################################################################
       Name: Placement Bill of Materials Generator

    Version: 4 (2-sided, top)
         By: Small Batch Assembly
        URL: www.smallbatchassembly.com
 SourceFile: femtoBeacon_dongle_r2.0.6_RGB.brd
   DateTime: 1/3/18 4:22 AM
      Units: inches
##########################################################################
REF,PACKAGE,VALUE,X,Y,ROTATION,
ASWITCH   , AS222-92LF            , AS222-92LF     , 1.1500, 0.5100, 0.0
BTN   , SPST_SMD            , DNP     , 0.4800, 0.2300, 0.0
C1   , PART            , 0.1uF     , 0.5100, 0.2700, 0.0
C2   , PART            , 0.1uF     , 0.7700, 0.6900, 180.0
C5   , _0402MP            , 2.2uF     , 0.7100, 0.8300, 180.0
C6   , _0402MP            , 2.2uF     , 0.7100, 0.7400, 0.0
C7   , PART            , 0.47uF     , 0.7000, 0.7000, 0.0
C8   , PART            , 0.1uF     , 0.9000, 0.2800, 90.0
C9   , PART            , 0.1uF     , 0.6500, 0.5200, 90.0
C10   , PART            , 0.1uF     , 0.7000, 0.6500, 180.0
C11   , _0402MP            , 1.2pF     , 1.2300, 0.6000, 180.0
C13   , PART            , DNP     , 1.1100, 0.6600, 180.0
C14   , PART            , 9pF     , 0.7200, 0.2500, 270.0
C15   , PART            , 9pF     , 0.7200, 0.3100, 270.0
C16   , PART            , 0.1uF     , 0.6500, 0.4600, 270.0
C17   , PART            , 0.1uF     , 0.8300, 0.3500, 0.0
C18   , PART            , 22pF     , 1.1500, 0.5900, 270.0
C19   , PART            , 22pF     , 1.1800, 0.5900, 270.0
C20   , PART            , 22pF     , 1.1200, 0.5900, 90.0
C21   , _0402MP            , 10uF     , 0.5300, 0.7700, 270.0
C22   , _0402MP            , 10uF     , 0.8600, 0.2800, 270.0
C23   , PART            , 22pF     , 1.1760, 0.3980, 90.0
C24   , PART            , 22pF     , 1.2400, 0.5400, 90.0
CN1   , USB_A-SMT            ,      , 0.4800, 0.5300, 90.0
FB1   , _0603MP            ,      , 0.4800, 0.7700, 90.0
FB2   , _0603MP            ,      , 0.6100, 0.6900, 0.0
FID1   , FIDUCIAL_1MM            , FIDUCIAL     , 0.1000, 0.3000, 0.0
FID2   , FIDUCIAL_1MM            , FIDUCIAL     , 0.1000, 0.8000, 0.0
FID3   , FIDUCIAL_1MM            , FIDUCIAL     , 1.4500, 0.8000, 0.0
L1   , _0603MP            , 1.8nH     , 1.2060, 0.6560, 0.0
L6   , _0603MP            , 10uH     , 0.8100, 0.2800, 90.0
LDO_VREG   , MCP1700T-3302E/TT            , MCP1700T-3302E/TT     , 0.6300, 0.7800, 270.0
R1   , PART            , 330     , 0.4800, 0.3100, 0.0
R2   , PART            , 10K     , 0.5100, 0.3500, 0.0
R4   , PART            , 330     , 0.9700, 0.2600, 0.0
R6   , PART            , 330     , 0.9700, 0.3000, 0.0
R7   , PART            , 330     , 0.9800, 0.3480, 0.0
RGBLED   , LRTB_R48G            , LRTB_R48G     , 1.0300, 0.2800, 270.0
U$6   , 0479480001            , 0479480001     , 1.2040, 0.7770, 90.0
U$12   , 0805_BALUN            , JOHANSON_2450BM15A0015E     , 1.0500, 0.5100, 270.0
U$76   , QFN32            , ATSAMR21E18A-MUT     , 0.8100, 0.5100, 90.0
UFLANT   , U.FL            , uFL     , 1.1860, 0.2900, 90.0
XOSCRF   , TSX-3225            , 16MHz     , 0.6200, 0.2800, 0.0

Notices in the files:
parts and their libraries:
microbuilder: This work is placed in the public domain, and may be freely used for commercial and non-commercial work with the following conditions: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
